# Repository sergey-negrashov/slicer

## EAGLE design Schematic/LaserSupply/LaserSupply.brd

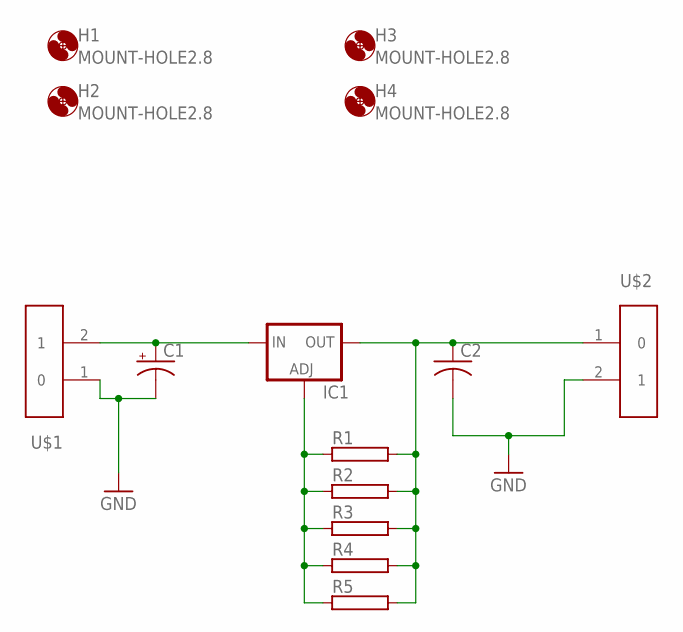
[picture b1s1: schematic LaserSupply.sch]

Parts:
C1: CPOL-USE2.5-5; E2,5-5
C2: C-US050-024X044; C050-024X044
H1, H2, H3, H4: MOUNT-HOLE2.8; 2,8
IC1: LM317TS; 317TS
R1, R2, R3, R4, R5: RRS1/4; RS1/4
U$1, U$2: ED2609

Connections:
GND: C1.-, C2.2, U$1.1 (0), U$2.2 (1)
unnamed: C1.+, IC1.3 (IN), U$1.2 (1)
unnamed: IC1.1 (ADJ), R1.1, R2.1, R3.1, R4.1, R5.1
unnamed: C2.1, IC1.2 (OUT), R1.2, R2.2, R3.2, R4.2, R5.2, U$2.1 (0)

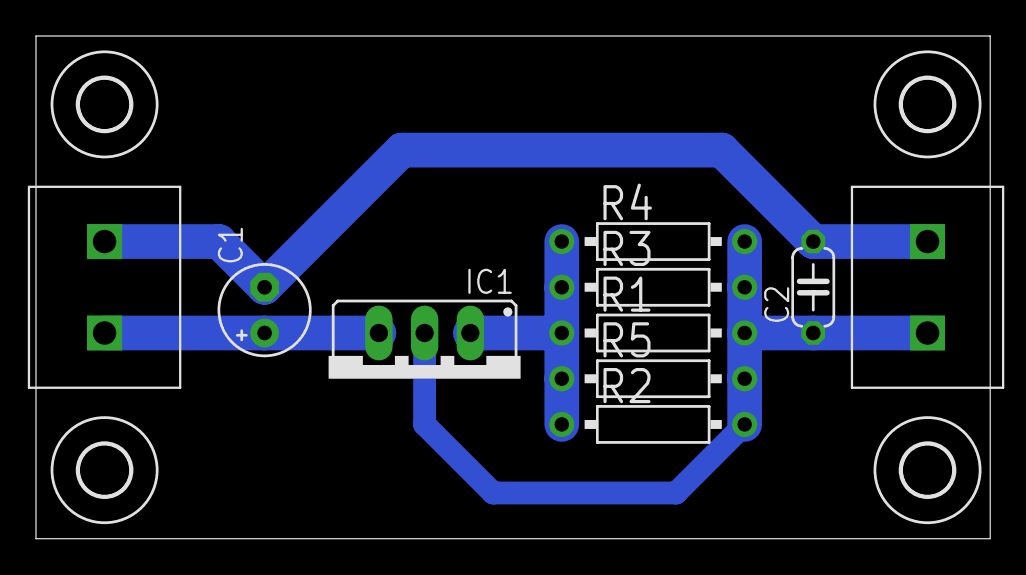
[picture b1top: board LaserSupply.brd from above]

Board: 2 copper layers, 53.0 x 27.9 mm, 14 parts (0 on the bottom side), 4 nets.

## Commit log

2016-05-07 Constant current source laser driver for 1A
